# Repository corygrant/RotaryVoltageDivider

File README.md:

# RotaryVoltageDivider

Works with Grayhill Series 56 rotary switches. 

Tested: 56DP30-01-1-AJN

Requires 13x 0805 1K resistors and/or 0R resistors (depending on number of positions)

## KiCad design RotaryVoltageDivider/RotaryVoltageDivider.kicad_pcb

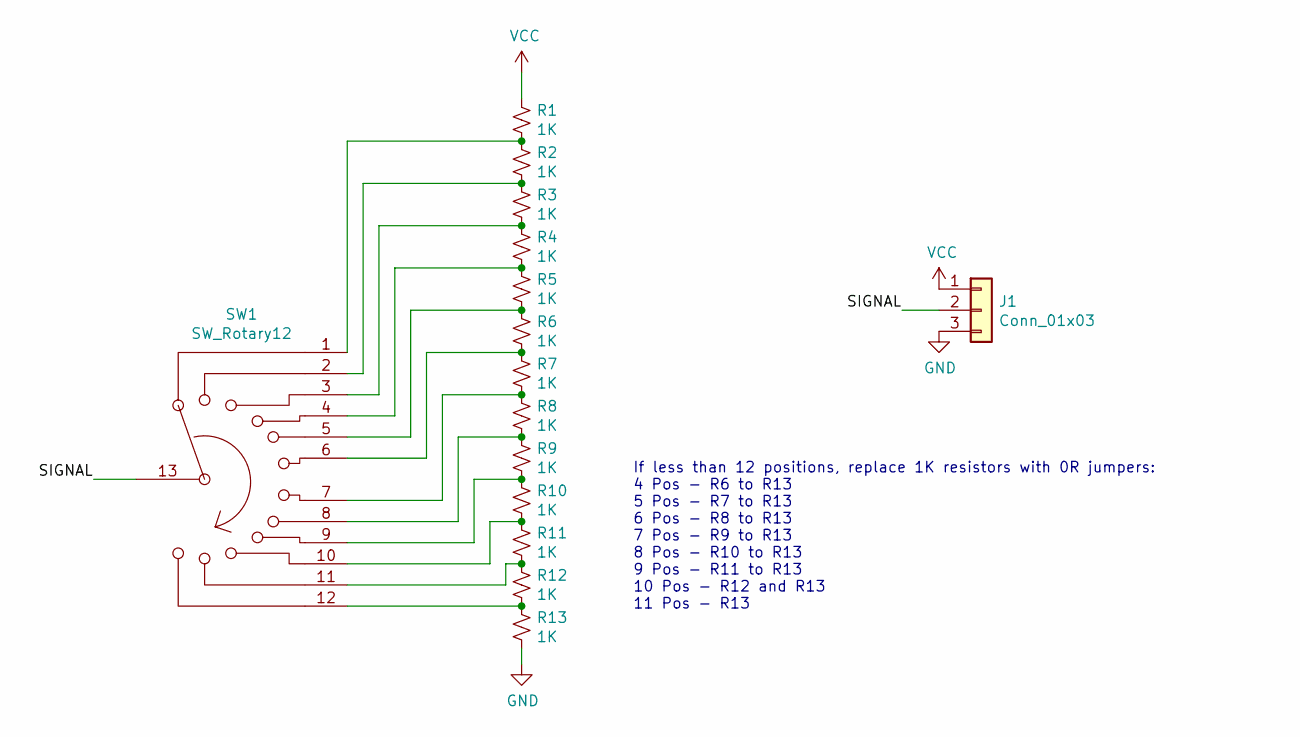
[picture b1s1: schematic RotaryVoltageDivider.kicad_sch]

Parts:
J1: Conn_01x03; PinHeader_1x03_P1.27mm_Vertical
R1, R2, R3, R4, R5, R6, R7, R8, R9, R10, R11, R12, R13: 1K; R_0805_2012Metric
SW1: SW_Rotary12; 56P30-01-1-XXN

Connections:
/SIGNAL: J1.2, SW1.13
GND: J1.3, R13.2
unnamed: R1.2, R2.1, SW1.1
unnamed: R2.2, R3.1, SW1.2
unnamed: R3.2, R4.1, SW1.3
unnamed: R4.2, R5.1, SW1.4
unnamed: R5.2, R6.1, SW1.5
unnamed: R6.2, R7.1, SW1.6
unnamed: R7.2, R8.1, SW1.7
unnamed: R8.2, R9.1, SW1.8
unnamed: R9.2, R10.1, SW1.9
unnamed: R10.2, R11.1, SW1.10
unnamed: R11.2, R12.1, SW1.11
unnamed: R12.2, R13.1, SW1.12
VCC: J1.1, R1.1

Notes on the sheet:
If less than 12 positions, replace 1K resistors with 0R jumpers: 4 Pos - R6 to R13 5 Pos - R7 to R13 6 Pos - R8 to R13 7 Pos - R9 to R13 8 Pos - R10 to R13 9 Pos - R11 to R13 10 Pos - R12 and R13 11 Pos - R13

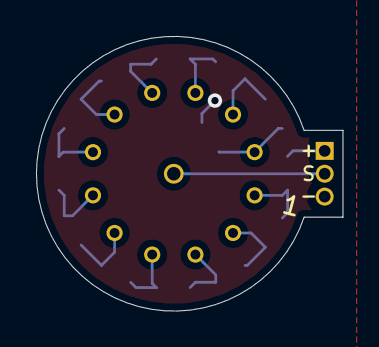
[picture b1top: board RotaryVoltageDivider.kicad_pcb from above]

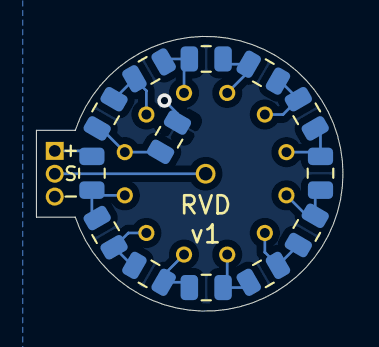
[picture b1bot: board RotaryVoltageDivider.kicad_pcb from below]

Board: 2 copper layers, 17.0 x 15.3 mm, 15 parts (14 on the bottom side), 15 nets.

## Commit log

2024-07-13 Added initial files
2024-09-06 Update to Kicad 8
